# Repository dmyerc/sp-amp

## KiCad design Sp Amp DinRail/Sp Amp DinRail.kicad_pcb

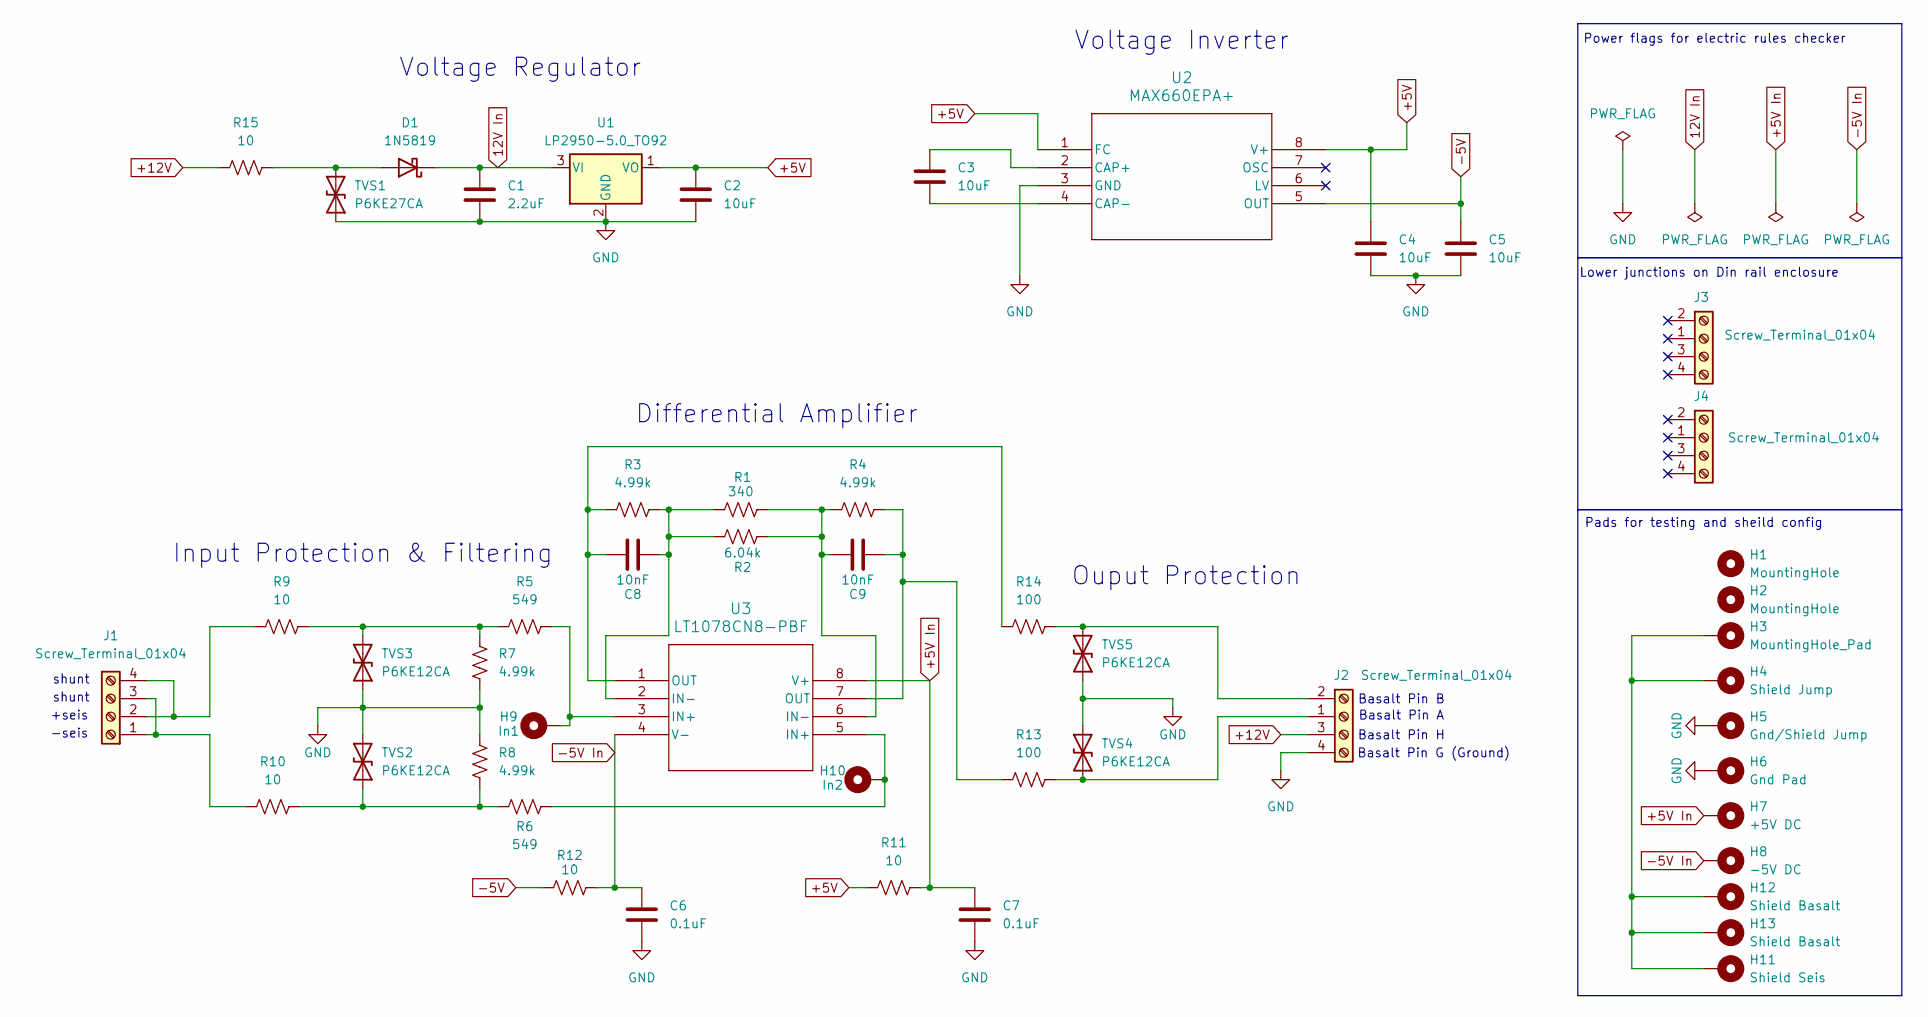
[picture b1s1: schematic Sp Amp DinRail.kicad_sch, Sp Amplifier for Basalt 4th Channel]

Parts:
C1: 2.2uF; CAP-TH_L6.0-W4.0-P5.00-D1.2
C2, C3, C4, C5: 10uF; CAP-TH_L5.9-W4.1-P5.08-D0.5
C6, C7: 0.1uF; CAP-TH_L8.5-W5.0-P5.00-D1.2
C8, C9: 10nF; CAP-TH_L4.9-W3.7-P5.08-D0.5
D1: 1N5819; DO-41_BD2.4-L4.7-P8.70-D0.9-FD
H1, H2: MountingHole; MountingHole_2.2mm_M2_DIN965_Pad
H3: MountingHole_Pad; MountingHole_2.2mm_M2_DIN965_Pad
H4: Shield Jump; Mounting Hole Small
H5: Gnd/Shield Jump; Mounting Hole Small
H6: Gnd Pad; Mounting Hole Small
H7: +5V DC; Mounting Hole Small
H8: -5V DC; Mounting Hole Small
H9: In1; Mounting Hole Small
H10: In2; Mounting Hole Small
H11: Shield Seis; Mounting Hole Mid
H12, H13: Shield Basalt; Mounting Hole Mid
J1, J2, J3, J4: Screw_Terminal_01x04; Molex Term Block 35 1x4 FOR PCB
R1: 340; RES-TH_BD2.5-L4.7-P8.70-D0.5
R2: 6.04k; RES-TH_BD3.3-L9.0-P13.00-D0.6
R3, R4, R7, R8: 4.99k; RES-TH_BD2.4-L6.3-P10.30-D0.6
R5, R6: 549; RES-TH_BD2.4-L6.3-P10.30-D0.6
R9, R10, R11, R12, R15: 10; RES-TH_BD2.2-L6.5-P10.50-D0.6
R13, R14: 100; RES-TH_BD2.4-L6.3-P10.30-D0.6
TVS1: P6KE27CA; DO-15_BD3.1-L6.7-P10.70-D0.9-BI
TVS2, TVS3, TVS4, TVS5: P6KE12CA; DO-15_BD3.1-L6.7-P10.70-D0.9-BI
U1: LP2950-5.0_TO92; TO-92-3_L4.9-W3.7-P1.27-L
U2: MAX660EPA+; DIP-8_L10.2-W10.2-P2.54-LS7.6-BL
U3: LT1078CN8-PBF; DIP-8_L10.2-W10.2-P2.54-LS7.6-BL

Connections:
12V In: C1.1, D1.1 (K), U1.3 (VI)
+5V: C2.1, C4.1, R11.2, U1.1 (VO), U2.1 (FC), U2.8 (V+)
+5V In: C7.1, H7.1, R11.1, U3.8 (V+)
+12V: J2.3, R15.1
-5V: C5.1, R12.2, U2.5 (OUT)
-5V In: C6.1, H8.1, R12.1, U3.4 (V-)
GND: C1.2, C2.2, C4.2, C5.2, C6.2, C7.2, H5.1, H6.1, J2.4, R7.1, R8.2, TVS1.1 (A1), TVS2.2 (A2), TVS3.1 (A1), TVS4.2 (A2), TVS5.1 (A1), U1.2 (GND), U2.3 (GND)
unnamed: C8.1, R1.1, R2.1, R3.2, U3.2 (IN-)
unnamed: C8.2, R3.1, R14.1, U3.1 (OUT)
unnamed: C9.1, R4.2, R13.1, U3.7 (OUT)
unnamed: C9.2, R1.2, R2.2, R4.1, U3.6 (IN-)
unnamed: D1.2 (A), R15.2, TVS1.2 (A2)
unnamed: H9.1, R5.2, U3.3 (IN+)
unnamed: H10.1, R6.2, U3.5 (IN+)
unnamed: H3.1, H4.1, H11.1, H12.1, H13.1
unnamed: J1.1, J1.3, R10.2
unnamed: J1.2, J1.4, R9.1
unnamed: J2.1, R13.2, TVS4.1 (A1)
unnamed: J2.2, R14.2, TVS5.2 (A2)
unnamed: R6.1, R8.1, R10.1, TVS2.1 (A1)
unnamed: R5.1, R7.2, R9.2, TVS3.2 (A2)
unnamed: C3.1, U2.2 (CAP+)
unnamed: C3.2, U2.4 (CAP-)

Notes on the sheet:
Differential Amplifier
shunt
Basalt Pin H
Basalt Pin B
-seis
+seis
Pads for testing and sheild config
Voltage Regulator
Voltage Inverter
Basalt Pin A
Input Protection & Filtering
Ouput Protection
Basalt Pin G (Ground)
Lower junctions on Din rail enclosure
Power flags for electric rules checker

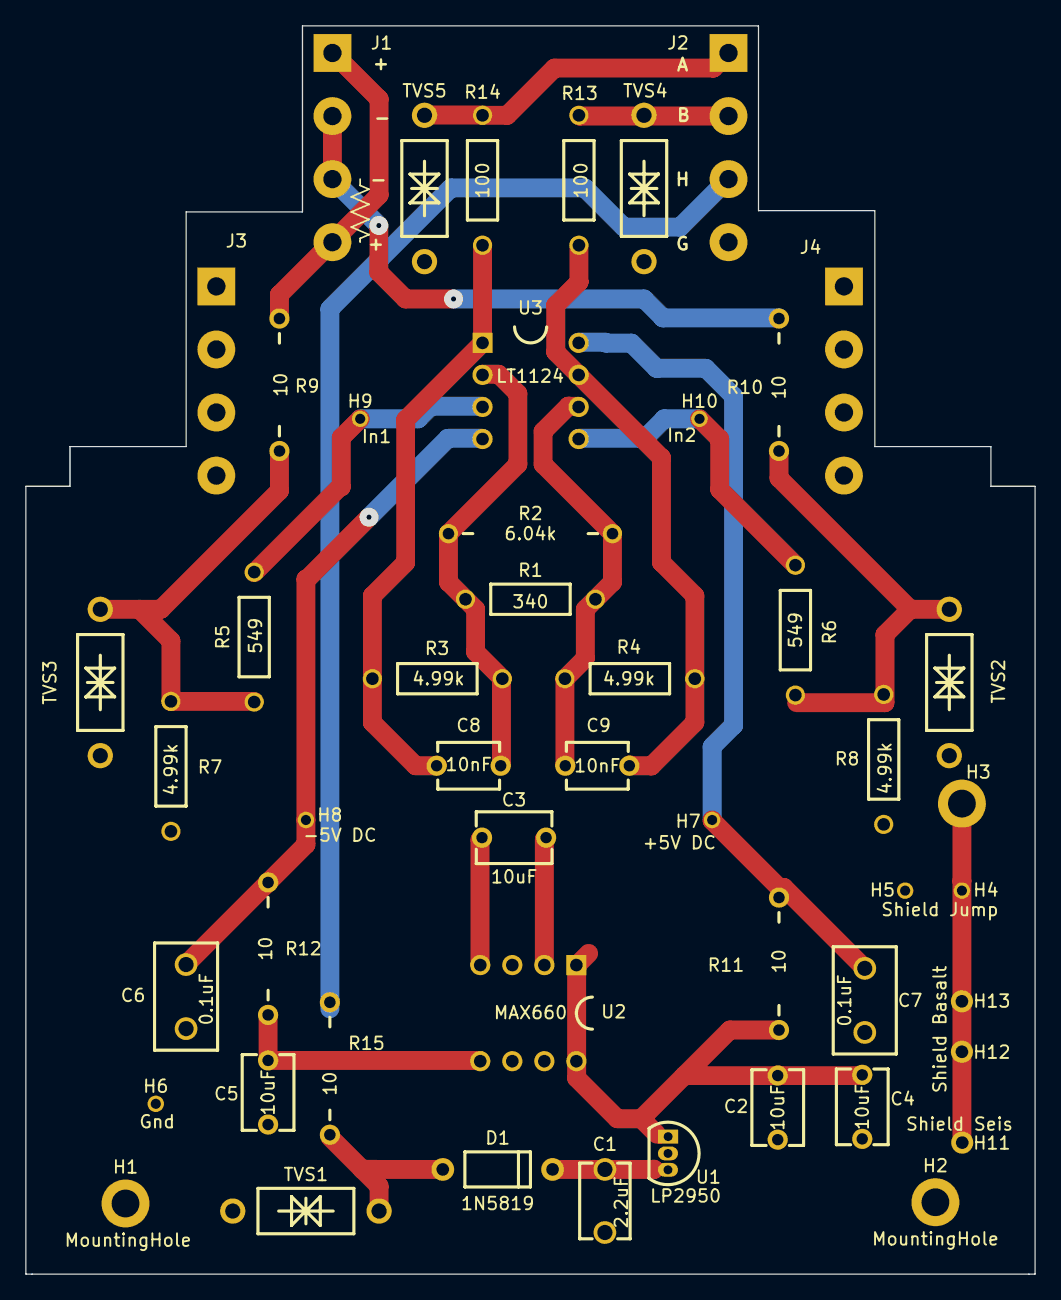
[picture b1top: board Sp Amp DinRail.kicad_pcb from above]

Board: 2 copper layers, 80.0 x 99.0 mm, 50 parts (0 on the bottom side), 23 nets.
